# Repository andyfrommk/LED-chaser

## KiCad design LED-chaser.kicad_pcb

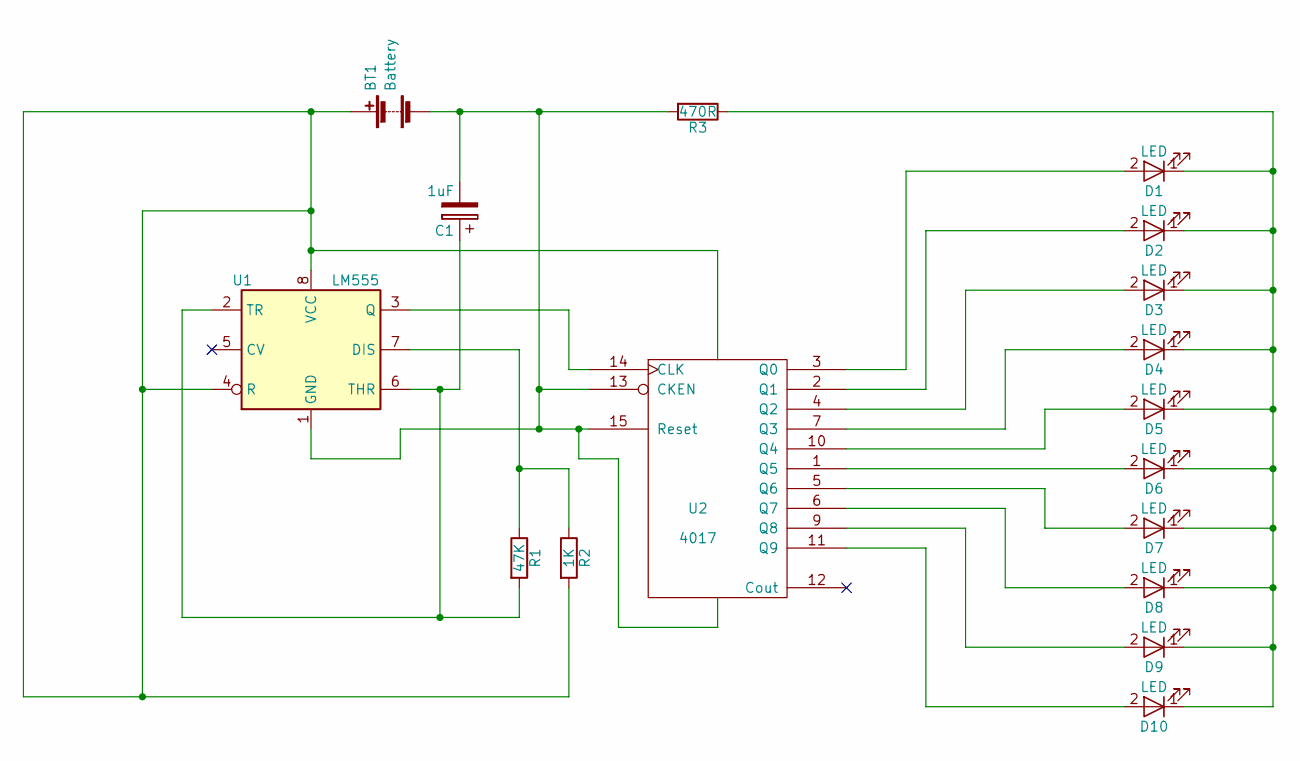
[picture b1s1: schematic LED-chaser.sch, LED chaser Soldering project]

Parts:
BT1: Battery; PINHEAD1-2
C1: 1uF; C_Radial_D5_L6_P2.5
D1, D2, D3, D4, D5, D6, D7, D8, D9, D10: LED; LED-5MM
R1: 47K; Resistor_Horizontal_RM7mm
R2: 1K; Resistor_Horizontal_RM7mm
R3: 470R; Resistor_Horizontal_RM7mm
U1: LM555; DIP-8_W7.62mm
U2: 4017; DIP-16_W7.62mm

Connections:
unnamed: C1.1, R1.2, U1.2 (TR), U1.6 (THR)
unnamed: D1.1 (K), D2.1 (K), D3.1 (K), D4.1 (K), D5.1 (K), D6.1 (K), D7.1 (K), D8.1 (K), D9.1 (K), D10.1 (K), R3.1
unnamed: D1.2 (A), U2.3 (Q0)
unnamed: D2.2 (A), U2.2 (Q1)
unnamed: D3.2 (A), U2.4 (Q2)
unnamed: D4.2 (A), U2.7 (Q3)
unnamed: D5.2 (A), U2.10 (Q4)
unnamed: D6.2 (A), U2.1 (Q5)
unnamed: D7.2 (A), U2.5 (Q6)
unnamed: D8.2 (A), U2.6 (Q7)
unnamed: D9.2 (A), U2.9 (Q8)
unnamed: D10.2 (A), U2.11 (Q9)
unnamed: R1.1, R2.1, U1.7 (DIS)
unnamed: U1.3 (Q), U2.14 (CLK)
VDD: BT1.1 (+), R2.2, U1.4 (R), U1.8 (VCC), U2.16 (VDD)
VSS: BT1.2 (-), C1.2, R3.2, U1.1 (GND), U2.8 (VSS), U2.13 (CKEN), U2.15 (Reset)

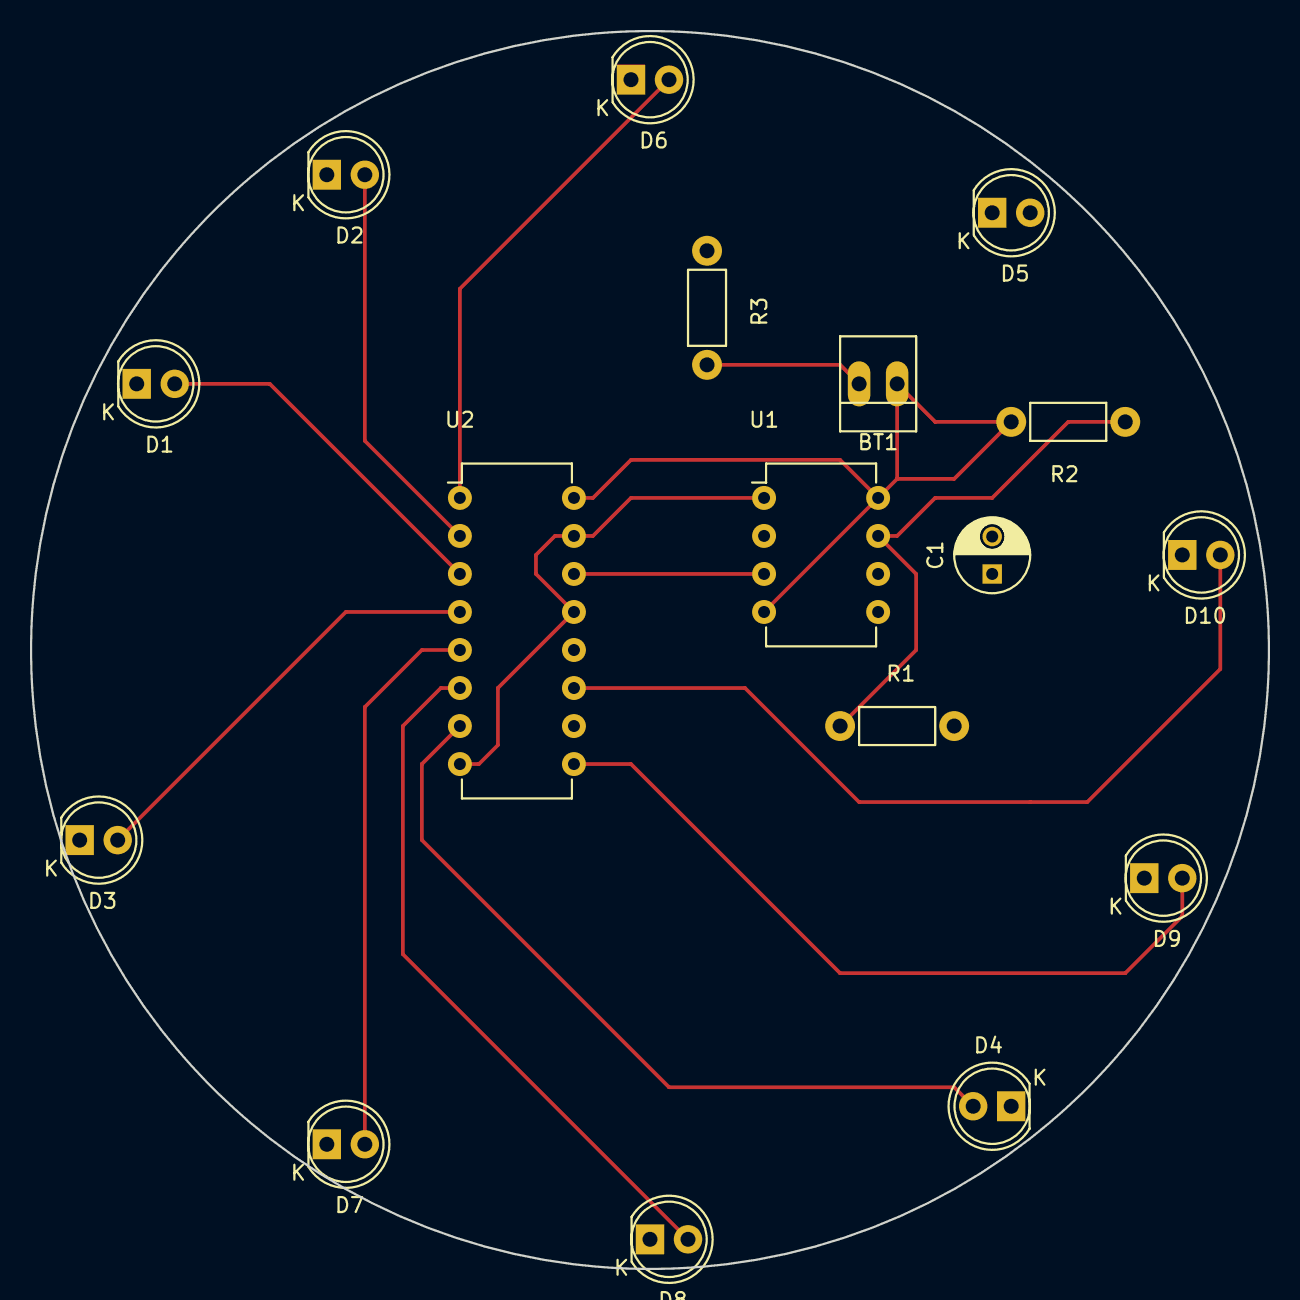
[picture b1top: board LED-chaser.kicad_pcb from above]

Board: 2 copper layers, 82.7 x 82.7 mm, 17 parts (0 on the bottom side), 16 nets.
